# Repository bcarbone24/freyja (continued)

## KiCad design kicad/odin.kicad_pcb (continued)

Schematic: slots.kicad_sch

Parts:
C139, C140, C141, C142, C144, C146, C148, C150, C152, C154, C156, C158, C160, C162: 100nF; C_0402_1005Metric; LCSC C1525
C143, C145, C147, C149, C151, C153, C155, C157, C159, C161: 10uF; C_0805_2012Metric; LCSC C15850
C163, C164, C165, C166: 22uF; C_0805_2012Metric; LCSC C86816
F1, F2, F5, F6, F9, F10, F13, F14, F17, F18, F21, F22, F25, F26, F29, F30, F33, F34, F37, F38: 500mA; F1206; LCSC C269115
F3, F7, F11, F15, F19, F23, F27, F31, F35, F39: 300mA; F1206; LCSC C22378340
F4, F8, F12, F16, F20, F24, F28, F32, F36, F40: 1.1A 33V; Fuse_TECHFUSE_SMD2018; LCSC C70150
J3, J5: WingTAT 2044-2X32G00SA; HDR-TH_64P-P2.54-V-F-R2-C32-S2.54-1; LCSC C49569844
J7, J8: PM254-2-08-Z-8.5; HDR-TH_16P-P2.54-V-F-R2-C8-S2.54; LCSC C2897409
J19, J20: 2.54-2*3P; HDR-TH_6P-P2.54-V-M-R2-C3-S2.54-1; LCSC C65114
J53, J54, J55, J56, J57, J58, J62, J63, J64, J65: XFCN PM254V-11-07-H85; HDR-TH_7P-P2.54-V-F; LCSC C2832270
MK65, MK66, MK67, MK68, MK69, MK70, MK71, MK72, MK76, MK77: BOOMELE 2.54-1x40P-21mm; cut to 1P; hand/wave sol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; HDR-TH_1P-P2.54-V-M-21MM-C51353; LCSC C51353
R96, R97: 10k; R_0603_1608Metric
U9, U10: SN74LXC8T245PWR; TSSOP-24_L7.8-W4.4-P0.65-LS6.4-BL_1; LCSC C4363995

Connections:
+1V8_IO: C139.1, C141.1, J19.5, J20.5, R96.1, R97.1, U9.1 (VCCA), U10.1 (VCCA); also elsewhere on the board
+2V5: J19.3, J20.3; also elsewhere on the board
+3V3: J19.1, J20.1; also elsewhere on the board
+3V3_EXT: F1.1, F3.1, F5.1, F7.1, F11.1, F15.1, F19.1, F23.1, F27.1, F31.1, F35.1, F39.1; also elsewhere on the board
+5V: C140.1, C142.1, U9.23 (VCCB), U9.24 (VCCB), U10.23 (VCCB), U10.24 (VCCB); also elsewhere on the board
+5V_EXT: F2.1, F6.1, F10.1, F14.1, F18.1, F22.1, F26.1, F30.1, F34.1, F38.1; also elsewhere on the board
AUX_RAIL: F4.1, F8.1, F12.1, F16.1, F20.1, F24.1, F28.1, F32.1, F36.1, F40.1; also elsewhere on the board
BUS5V0_DIR: U9.2 (DIR); also elsewhere on the board
BUS5V0_IO0: U9.3 (A1); also elsewhere on the board
BUS5V0_IO1: U9.4 (A2); also elsewhere on the board
BUS5V0_IO2: U9.5 (A3); also elsewhere on the board
BUS5V0_IO3: U9.6 (A4); also elsewhere on the board
BUS5V0_IO4: U9.7 (A5); also elsewhere on the board
BUS5V0_IO5: U9.8 (A6); also elsewhere on the board
BUS5V0_IO6: U9.9 (A7); also elsewhere on the board
BUS5V0_IO7: U9.10 (A8); also elsewhere on the board
BUS5V0_OE_N: R96.2, U9.22 (~OE); also elsewhere on the board
BUS5V0_PIN0: J7.1, U9.21 (B1)
BUS5V0_PIN1: J7.2, U9.20 (B2)
BUS5V0_PIN2: J7.3, U9.19 (B3)
BUS5V0_PIN3: J7.4, U9.18 (B4)
BUS5V0_PIN4: J7.7, U9.17 (B5)
BUS5V0_PIN5: J7.8, U9.16 (B6)
BUS5V0_PIN6: J7.9, U9.15 (B7)
BUS5V0_PIN7: J7.10, U9.14 (B8)
BUS5V1_DIR: U10.2 (DIR); also elsewhere on the board
BUS5V1_IO0: U10.3 (A1); also elsewhere on the board
BUS5V1_IO1: U10.4 (A2); also elsewhere on the board
BUS5V1_IO2: U10.5 (A3); also elsewhere on the board
BUS5V1_IO3: U10.6 (A4); also elsewhere on the board
BUS5V1_IO4: U10.7 (A5); also elsewhere on the board
BUS5V1_IO5: U10.8 (A6); also elsewhere on the board
BUS5V1_IO6: U10.9 (A7); also elsewhere on the board
BUS5V1_IO7: U10.10 (A8); also elsewhere on the board
BUS5V1_OE_N: R97.2, U10.22 (~OE); also elsewhere on the board
BUS5V1_PIN0: J8.1, U10.21 (B1)
BUS5V1_PIN1: J8.2, U10.20 (B2)
BUS5V1_PIN2: J8.3, U10.19 (B3)
BUS5V1_PIN3: J8.4, U10.18 (B4)
BUS5V1_PIN4: J8.7, U10.17 (B5)
BUS5V1_PIN5: J8.8, U10.16 (B6)
BUS5V1_PIN6: J8.9, U10.15 (B7)
BUS5V1_PIN7: J8.10, U10.14 (B8)
GND: C139.2, C140.2, C141.2, C142.2, C143.2, C144.2, C145.2, C146.2, C147.2, C148.2, C149.2, C150.2, C151.2, C152.2, C153.2, C154.2, C155.2, C156.2, C157.2, C158.2, C159.2, C160.2, C161.2, C162.2, C163.2, C164.2, C165.2, C166.2, J3.5, J3.6, J3.11, J3.12, J3.21, J3.22, J3.27, J3.28, J3.37, J3.38, J3.43, J3.44, J3.53, J3.54, J3.59, J3.60, J5.5, J5.6, J5.11, J5.12, J5.21, J5.22, J5.27, J5.28, J5.37, J5.38, J5.43, J5.44, J5.53, J5.54, J5.59, J5.60, J7.5, J7.6, J7.11, J7.12, J8.5, J8.6, J8.11, J8.12, J53.2, J53.4, J53.6, J54.2, J54.4, J54.6, J55.2, J55.4, J55.6, J56.2, J56.4, J56.6, J57.2, J57.4, J57.6, J58.2, J58.4, J58.6, J62.2, J62.4, J62.6, J63.2, J63.4, J63.6, J64.2, J64.4, J64.6, J65.2, J65.4, J65.6, MK65.1, MK66.1, MK67.1, MK68.1, MK69.1, MK70.1, MK71.1, MK72.1, MK76.1, MK77.1, U9.11 (GND), U9.12 (GND), U9.13 (GND), U10.11 (GND), U10.12 (GND), U10.13 (GND); also elsewhere on the board
SLOTA_IO0: J3.1; also elsewhere on the board
SLOTA_IO1: J3.2; also elsewhere on the board
SLOTA_IO2: J3.3; also elsewhere on the board
SLOTA_IO3: J3.4; also elsewhere on the board
SLOTA_IO4: J3.7; also elsewhere on the board
SLOTA_IO5: J3.8; also elsewhere on the board
SLOTA_IO6: J3.9; also elsewhere on the board
SLOTA_IO7: J3.10; also elsewhere on the board
SLOTA_IO8: J3.13; also elsewhere on the board
SLOTA_IO9: J3.14; also elsewhere on the board
SLOTA_IO10: J3.15; also elsewhere on the board
SLOTA_IO11: J3.16; also elsewhere on the board
SLOTB_IO0: J3.17; also elsewhere on the board
SLOTB_IO1: J3.18; also elsewhere on the board
SLOTB_IO2: J3.19; also elsewhere on the board
SLOTB_IO3: J3.20; also elsewhere on the board
SLOTB_IO4: J3.23; also elsewhere on the board
SLOTB_IO5: J3.24; also elsewhere on the board
SLOTB_IO6: J3.25; also elsewhere on the board
SLOTB_IO7: J3.26; also elsewhere on the board
SLOTB_IO8: J3.29; also elsewhere on the board
SLOTB_IO9: J3.30; also elsewhere on the board
SLOTB_IO10: J3.31; also elsewhere on the board
SLOTB_IO11: J3.32; also elsewhere on the board
SLOTC_IO0: J3.33; also elsewhere on the board
SLOTC_IO1: J3.34; also elsewhere on the board
SLOTC_IO2: J3.35; also elsewhere on the board
SLOTC_IO3: J3.36; also elsewhere on the board
SLOTC_IO4: J3.39; also elsewhere on the board
SLOTC_IO5: J3.40; also elsewhere on the board
SLOTC_IO6: J3.41; also elsewhere on the board
SLOTC_IO7: J3.42; also elsewhere on the board
SLOTC_IO8: J3.45; also elsewhere on the board
SLOTC_IO9: J3.46; also elsewhere on the board
SLOTC_IO10: J3.47; also elsewhere on the board
SLOTC_IO11: J3.48; also elsewhere on the board
SLOTD_IO0: J3.49; also elsewhere on the board
SLOTD_IO1: J3.50; also elsewhere on the board
SLOTD_IO2: J3.51; also elsewhere on the board
SLOTD_IO3: J3.52; also elsewhere on the board
SLOTD_IO4: J3.55; also elsewhere on the board
SLOTD_IO5: J3.56; also elsewhere on the board
SLOTD_IO6: J3.57; also elsewhere on the board
SLOTD_IO7: J3.58; also elsewhere on the board
SLOTD_IO8: J3.61; also elsewhere on the board
SLOTD_IO9: J3.62; also elsewhere on the board
SLOTD_IO10: J3.63; also elsewhere on the board
SLOTD_IO11: J3.64; also elsewhere on the board
SLOTE_IO0: J5.64; also elsewhere on the board
SLOTE_IO1: J5.63; also elsewhere on the board
SLOTE_IO2: J5.62; also elsewhere on the board
SLOTE_IO3: J5.61; also elsewhere on the board
SLOTE_IO4: J5.58; also elsewhere on the board
SLOTE_IO5: J5.57; also elsewhere on the board
SLOTE_IO6: J5.56; also elsewhere on the board
SLOTE_IO7: J5.55; also elsewhere on the board
SLOTE_IO8: J5.52; also elsewhere on the board
SLOTE_IO9: J5.51; also elsewhere on the board
SLOTE_IO10: J5.50; also elsewhere on the board
SLOTE_IO11: J5.49; also elsewhere on the board
SLOTF_IO0: J5.48; also elsewhere on the board
SLOTF_IO1: J5.47; also elsewhere on the board
SLOTF_IO2: J5.46; also elsewhere on the board
SLOTF_IO3: J5.45; also elsewhere on the board
SLOTF_IO4: J5.42; also elsewhere on the board
SLOTF_IO5: J5.41; also elsewhere on the board
SLOTF_IO6: J5.40; also elsewhere on the board
SLOTF_IO7: J5.39; also elsewhere on the board
SLOTF_IO8: J5.36; also elsewhere on the board
SLOTF_IO9: J5.35; also elsewhere on the board
SLOTF_IO10: J5.34; also elsewhere on the board
SLOTF_IO11: J5.33; also elsewhere on the board
SLOTG_IO0: J5.32; also elsewhere on the board
SLOTG_IO1: J5.31; also elsewhere on the board
SLOTG_IO2: J5.30; also elsewhere on the board
SLOTG_IO3: J5.29; also elsewhere on the board
SLOTG_IO4: J5.26; also elsewhere on the board
SLOTG_IO5: J5.25; also elsewhere on the board
SLOTG_IO6: J5.24; also elsewhere on the board
SLOTG_IO7: J5.23; also elsewhere on the board
SLOTG_IO8: J5.20; also elsewhere on the board
SLOTG_IO9: J5.19; also elsewhere on the board
SLOTG_IO10: J5.18; also elsewhere on the board
SLOTG_IO11: J5.17; also elsewhere on the board
SLOTH_IO0: J5.16; also elsewhere on the board
SLOTH_IO1: J5.15; also elsewhere on the board
SLOTH_IO2: J5.14; also elsewhere on the board
SLOTH_IO3: J5.13; also elsewhere on the board
SLOTH_IO4: J5.10; also elsewhere on the board
SLOTH_IO5: J5.9; also elsewhere on the board
SLOTH_IO6: J5.8; also elsewhere on the board
SLOTH_IO7: J5.7; also elsewhere on the board
SLOTH_IO8: J5.4; also elsewhere on the board
SLOTH_IO9: J5.3; also elsewhere on the board
SLOTH_IO10: J5.2; also elsewhere on the board
SLOTH_IO11: J5.1; also elsewhere on the board
SLOT_A_3V3: C148.1, F11.2, J53.3
SLOT_A_5V: F10.2, J53.5
SLOT_A_AUX: F12.2, J53.7
SLOT_A_PIN_VOLTAGE: C147.1, F9.2, J53.1
SLOT_B_3V3: C150.1, F15.2, J62.3
SLOT_B_5V: F14.2, J62.5
SLOT_B_AUX: F16.2, J62.7
SLOT_B_PIN_VOLTAGE: C149.1, F13.2, J62.1
SLOT_C_3V3: C152.1, F19.2, J54.3
SLOT_C_5V: F18.2, J54.5
SLOT_C_AUX: F20.2, J54.7
SLOT_C_PIN_VOLTAGE: C151.1, F17.2, J54.1
SLOT_D_3V3: C154.1, F23.2, J63.3
SLOT_D_5V: F22.2, J63.5
SLOT_D_AUX: F24.2, J63.7
SLOT_D_PIN_VOLTAGE: C153.1, F21.2, J63.1
SLOT_E_3V3: C156.1, F27.2, J55.3
SLOT_E_5V: F26.2, J55.5
SLOT_E_AUX: F28.2, J55.7
SLOT_E_PIN_VOLTAGE: C155.1, F25.2, J55.1
SLOT_F_3V3: C158.1, F31.2, J64.3
SLOT_F_5V: F30.2, J64.5
SLOT_F_AUX: F32.2, J64.7
SLOT_F_PIN_VOLTAGE: C157.1, F29.2, J64.1
SLOT_G_3V3: C160.1, F35.2, J56.3
SLOT_G_5V: F34.2, J56.5
SLOT_G_AUX: F36.2, J56.7
SLOT_G_PIN_VOLTAGE: C159.1, F33.2, J56.1
SLOT_H_3V3: C162.1, F39.2, J65.3
SLOT_H_5V: F38.2, J65.5
SLOT_H_AUX: F40.2, J65.7
SLOT_H_PIN_VOLTAGE: C161.1, F37.2, J65.1
SLOT_L_3V3: C144.1, F3.2, J57.3
SLOT_L_5V: F2.2, J57.5
SLOT_L_AUX: F4.2, J57.7
SLOT_L_PIN_VOLTAGE: C143.1, F1.2, J57.1
SLOT_M_3V3: C146.1, F7.2, J58.3
SLOT_M_5V: F6.2, J58.5
SLOT_M_AUX: F8.2, J58.7
SLOT_M_PIN_VOLTAGE: C145.1, F5.2, J58.1
VCCIO_1: C163.1, C164.1, J19.2, J19.4, J19.6; also elsewhere on the board
VCCIO_1_EXT: F9.1, F13.1, F17.1, F21.1; also elsewhere on the board
VCCIO_2: C165.1, C166.1, J20.2, J20.4, J20.6; also elsewhere on the board
VCCIO_2_EXT: F25.1, F29.1, F33.1, F37.1; also elsewhere on the board

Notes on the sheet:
SLOTS — Ten keyed extension ports, branch fusing and level shifting — HW 0.1.0-proto.1
5V BUS 0 converter
Lets the FPGA (3.3 V) talk to 5 V extensions on slot L. U9 shifts eight lines between 3.3 V and 5 V, all in one direction at a time (BUS5V0_DIR). It stays off until the FPGA pulls BUS5V0_OE_N low; the pull-up keeps the bus off while the FPGA is still loading.
5V BUS 1 converter
Same as 5V BUS 0, for slot M: U10 shifts eight lines between the FPGA's 3.3 V and 5 V, direction BUS5V1_DIR, off until BUS5V1_OE_N goes low.
SHIELD HEADER ABCD
One long 2x32 socket on the right edge carrying the signals of slots A, B, C and D: twelve FPGA pins each (bank 15), with grounds between groups. Their voltage is whatever J19 selects.
SHIELD HEADER EFGH
One long 2x32 socket on the left edge carrying the signals of slots E, F, G and H: twelve FPGA pins each (bank 34), voltage set by J20.
SHIELD HEADER L
The signal socket of slot L (5V BUS 0): eight 5 V data lines from U9, with four grounds between them.
SHIELD HEADER M
The signal socket of slot M (5V BUS 1): eight 5 V data lines from U10, with four grounds between them.
SLOT L branches
Power for whatever is plugged into slot L. The 1x7 power socket carries PIN V (3.3 V), 3.3 V, 5 V and AUX, each beside a ground, and each through its own resettable fuse, so a short on one extension trips only that slot's fuse and the rest of the board keeps running. The long grounded pin in front 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
SLOT M branches
Power for whatever is plugged into slot M. The 1x7 power socket carries PIN V (3.3 V), 3.3 V, 5 V and AUX, each beside a ground, and each through its own resettable fuse, so a short on one extension trips only that slot's fuse and the rest of the board keeps running. The long grounded pin in front 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
SLOT A branches
Power for whatever is plugged into slot A. The 1x7 power socket carries PIN V (the J19 voltage), 3.3 V, 5 V and AUX, each beside a ground, and each through its own resettable fuse, so a short on one extension trips only that slot's fuse and the rest of the board keeps running. The long grounded pin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
SLOT B branches
Power for whatever is plugged into slot B. The 1x7 power socket carries PIN V (the J19 voltage), 3.3 V, 5 V and AUX, each beside a ground, and each through its own resettable fuse, so a short on one extension trips only that slot's fuse and the rest of the board keeps running. The long grounded pin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
SLOT C branches
Power for whatever is plugged into slot C. The 1x7 power socket carries PIN V (the J19 voltage), 3.3 V, 5 V and AUX, each beside a ground, and each through its own resettable fuse, so a short on one extension trips only that slot's fuse and the rest of the board keeps running. The long grounded pin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
SLOT D branches
Power for whatever is plugged into slot D. The 1x7 power socket carries PIN V (the J19 voltage), 3.3 V, 5 V and AUX, each beside a ground, and each through its own resettable fuse, so a short on one extension trips only that slot's fuse and the rest of the board keeps running. The long grounded pin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
SLOT E branches
Power for whatever is plugged into slot E. The 1x7 power socket carries PIN V (the J20 voltage), 3.3 V, 5 V and AUX, each beside a ground, and each through its own resettable fuse, so a short on one extension trips only that slot's fuse and the rest of the board keeps running. The long grounded pin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
SLOT F branches
Power for whatever is plugged into slot F. The 1x7 power socket carries PIN V (the J20 voltage), 3.3 V, 5 V and AUX, each beside a ground, and each through its own resettable fuse, so a short on one extension trips only that slot's fuse and the rest of the board keeps running. The long grounded pin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
SLOT G branches
Power for whatever is plugged into slot G. The 1x7 power socket carries PIN V (the J20 voltage), 3.3 V, 5 V and AUX, each beside a ground, and each through its own resettable fuse, so a short on one extension trips only that slot's fuse and the rest of the board keeps running. The long grounded pin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
SLOT H branches
Power for whatever is plugged into slot H. The 1x7 power socket carries PIN V (the J20 voltage), 3.3 V, 5 V and AUX, each beside a ground, and each through its own resettable fuse, so a short on one extension trips only that slot's fuse and the rest of the board keeps running. The long grounded pin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
VCCIO_1 selector
Jumper that picks the signal voltage of slots A-D: one shunt on J19 selects 3.3, 2.5 or 1.8 V. It powers FPGA bank 15 and the PIN V pin of those four slots. One position only; change it with the board unpowered.
VCCIO_2 selector
Jumper that picks the signal voltage of slots E-H (J20): 3.3, 2.5 or 1.8 V for FPGA bank 34 and those slots' PIN V pin.
Power flags for the rails made on this page

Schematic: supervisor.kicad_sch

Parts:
C116, C117, C118, C119, C120, C121, C122, C123, C124, C125, C126, C127, C128, C129, C135, C136, C138: 100nF; C_0402_1005Metric; LCSC C1525
C130, C131, C132: 4.7uF; C_0603_1608Metric; LCSC C277476
C133, C134: 15pF; C_0402_1005Metric
C137: 1uF; C_0402_1005Metric
D6: ESDA6V1BC6; SOT-23-6_L2.9-W1.6-P0.95-LS2.8-BR; LCSC C495220
D7: SMBJ13A-TR; SMB_L4.6-W3.6-LS5.3-RD; LCSC C133675
D9, D10, D11: F.0603.00025/P2-0603G1TS2-06T-002; LED0603-RD_GREEN; LCSC C7496818
J1: USB-C; USB_C_Receptacle_HCTL_HC-TYPE-C-16P-01A_Odin; LCSC C2894897
J2: FPGA JTAG; IDC-TH_10P-P2.54_C5665; LCSC C5665
J51: CTRL SWD; CONN-SMD-3P-P1.00_BM03B-SRSS-TB-LF-SN; LCSC C160389
J52: PZ254V-11-02P; HDR-TH_2P-P2.54-V-M; LCSC C492401
L1: 3.3uH AOTA-B201610S3R3-101-T; IND-SMD_L2.0-W1.6_AOTA-B201610S3R3-101-T; LCSC C42411119
Q3: BSS138LT1G; SOT-23-3_L2.9-W1.6-P1.90-LS2.8-BR; LCSC C82045
R8, R14, R15, R16, R17, R18, R19, R20, R21, R22, R23, R24, R25, R26, R27, R28, R29, R30, R31, R32: 33; R_0402_1005Metric; LCSC C25105
R9, R10, R12, R128, R129, R130: 1k; R_0402_1005Metric; LCSC C11702
R11, R172: 10k; R_0402_1005Metric
R13: 10k; R_0402_1005Metric; not fitted
R33: 0; R_0402_1005Metric
R34: 10k; R_0603_1608Metric
R170, R171: 27; R_0402_1005Metric
R173: 100k; R_0402_1005Metric; LCSC C25741
SW1: CTRL BOOT; KEY-SMD_B3U-1000PM; LCSC C231329
U7: RP2350B; QFN-80_L10.0-W10.0-P0.40-TL-EP3.4; LCSC C42415655
U8: W25Q32JVZP; WSON-8_L6.0-W5.0-P1.27-BL-EP; LCSC C571260
U18: CH224K; ESSOP-10_L4.9-W3.9-P1.0-LS6.0-TL-EP; LCSC C970725
U20: SN74CB3Q3384APWR; TSSOP-24_L7.8-W4.4-P0.65-LS6.4-BL; LCSC C469874
Y1: 12MHz ABM8-272-T3; CRYSTAL-SMD_4P-L3.2-W2.5-BL; LCSC C20625731

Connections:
+1V1: C127.1, C128.1, C129.1, C131.1, L1.1, U7.10 (DVDD), U7.32 (DVDD), U7.51 (DVDD), U7.65 (VREG_FB)
+3V3: C116.1, C117.1, C118.1, C119.1, C120.1, C121.1, C122.1, C123.1, C124.1, C125.1, C126.1, C130.1, C136.1, C138.1, J2.1, J52.1, R8.1, R10.1, R11.1, R13.1, R128.1, R129.1, R130.1, U7.5 (IOVDD), U7.15 (IOVDD), U7.24 (IOVDD), U7.29 (IOVDD), U7.41 (IOVDD), U7.50 (IOVDD), U7.59 (ADC_AVDD), U7.60 (IOVDD), U7.64 (VREG_VIN), U7.68 (USB_OTP_VDD), U7.69 (QSPI_IOVDD), U7.76 (IOVDD), U8.8 (VCC), U20.13 (~2OE), U20.24 (VCC); also elsewhere on the board
BOOTSEL_SW: R12.2, SW1.1
CFG_CCLK: R21.2; also elsewhere on the board
CFG_DONE: R20.2; also elsewhere on the board
CFG_INIT_B: R19.2; also elsewhere on the board
CFG_PROG_B: R18.2; also elsewhere on the board
CORE_1V0_GOOD: U7.47 (GPIO38); also elsewhere on the board
DBG_TCK: R27.2; also elsewhere on the board
DBG_TDI: R29.2; also elsewhere on the board
DBG_TDO: R30.2; also elsewhere on the board
DBG_TMS: R28.2; also elsewhere on the board
EN_1V0: U7.25 (GPIO24); also elsewhere on the board
EN_1V2: U7.26 (GPIO25); also elsewhere on the board
EN_2V5: U7.22 (GPIO22); also elsewhere on the board
EXTERNAL_JTAG_SELECTED: J52.2, R34.1, U20.1 (~1OE)
EXT_EN: U7.6 (GPIO8); also elsewhere on the board
EXT_FAULT: U7.43 (GPIO34); also elsewhere on the board
FLASH_CS_B: R22.2; also elsewhere on the board
FLASH_D0_MOSI: R23.2; also elsewhere on the board
FLASH_D1_MISO: R24.2; also elsewhere on the board
FLASH_D2_WP: R25.2; also elsewhere on the board
FLASH_D3_HOLD: R26.2; also elsewhere on the board
GND: C116.2, C117.2, C118.2, C119.2, C120.2, C121.2, C122.2, C123.2, C124.2, C125.2, C126.2, C127.2, C128.2, C129.2, C130.2, C131.2, C132.2, C133.2, C134.2, C135.2, C136.2, C137.2, C138.2, D6.2 (COM), D6.5 (COM), D7.2 (A), J1.A1 (GND), J1.A12 (GND), J1.B1 (GND), J1.B12 (GND), J1.SH (SHIELD), J2.2, J2.4, J2.6, J2.8, J2.10, J51.2, Q3.2 (S), R34.2, R173.2, SW1.2, U7.62 (VREG_PGND), U7.81 (GND), U8.4 (GND), U8.9 (EP), U18.2 (CFG2), U18.3 (CFG3), U18.11 (GND), U20.12 (GND), Y1.2 (G), Y1.4 (G); also elsewhere on the board
JTAG_TCK: J2.5, U20.2 (1B1); also elsewhere on the board
JTAG_TDI: J2.9, U20.6 (1B3); also elsewhere on the board
JTAG_TDO: J2.7, R33.2; also elsewhere on the board
JTAG_TDO_SW: R33.1, U20.9 (1B4)
JTAG_TMS: J2.3, U20.5 (1B2); also elsewhere on the board
LED_HEARTBEAT_A: D9.2 (A), R128.2
LED_HEARTBEAT_N: D9.1 (C), U7.44 (GPIO35)
LED_USER1_A: D10.2 (A), R129.2
LED_USER1_N: D10.1 (C), U7.45 (GPIO36)
LED_USER2_A: D11.2 (A), R130.2
LED_USER2_N: D11.1 (C), U7.46 (GPIO37)
MON_1V0: U7.56 (GPIO45/ADC5); also elsewhere on the board
MON_1V8: U7.55 (GPIO44/ADC4); also elsewhere on the board
MON_2V5: U7.54 (GPIO43/ADC3); also elsewhere on the board
MON_3V3: U7.53 (GPIO42/ADC2); also elsewhere on the board
MON_5V: U7.52 (GPIO41/ADC1); also elsewhere on the board
MON_VCCIO_1: U7.57 (GPIO46/ADC6); also elsewhere on the board
MON_VCCIO_2: U7.58 (GPIO47/ADC7); also elsewhere on the board
MON_VSYS: U7.49 (GPIO40/ADC0); also elsewhere on the board
PD_CFG1: Q3.3 (D), R172.2, U18.9 (CFG1)
PD_PG: R11.2, U7.38 (GPIO30), U18.10 (PG)
PD_REQ_9V: Q3.1 (G), R173.1, U7.28 (GPIO27); also elsewhere on the board
PD_VDD: C137.1, R172.1, U18.1 (VDD)
SB_UART_RX: R31.2; also elsewhere on the board
SB_UART_TX: R32.2; also elsewhere on the board
SUPF_CLK: U7.71 (QSPI_SCLK), U8.6 (CLK)
SUPF_CS: R12.1, R13.2, U7.75 (~QSPI_SS), U8.1 (~CS)
SUPF_D0: U7.72 (QSPI_SD0), U8.5 (DI/IO_{0})
SUPF_D1: U7.74 (QSPI_SD1), U8.2 (DO/IO_{1})
SUPF_D2: U7.73 (QSPI_SD2), U8.3 (~WP/IO_{2})
SUPF_D3: U7.70 (QSPI_SD3), U8.7 (~HOLD/~RESET/IO_{3})
SUP_CCLK: R21.1, U7.8 (GPIO10)
SUP_DBG_TCK: R27.1, U7.14 (GPIO15)
SUP_DBG_TDI: R29.1, U7.17 (GPIO17)
SUP_DBG_TDO: R30.1, U7.18 (GPIO18)
SUP_DBG_TMS: R28.1, U7.16 (GPIO16)
SUP_DONE: R20.1, U7.3 (GPIO6)
SUP_FCS_B: R22.1, U7.7 (GPIO9)
SUP_FD0: R23.1, U7.9 (GPIO11)
SUP_FD1: R24.1, U7.11 (GPIO12)
SUP_FD2: R25.1, U7.12 (GPIO13)
SUP_FD3: R26.1, U7.4 (GPIO7)
SUP_INIT_B: R19.1, U7.2 (GPIO5)
SUP_JTAG_TCK: R14.1, U7.77 (GPIO0)
SUP_JTAG_TDI: R16.1, U7.79 (GPIO2)
SUP_JTAG_TDO: R17.1, U7.80 (GPIO3)
SUP_JTAG_TMS: R15.1, U7.78 (GPIO1)
SUP_LX: L1.2, U7.63 (VREG_LX)
SUP_PROG_B: R18.1, U7.1 (GPIO4)
SUP_RUN: C135.1, R10.2, U7.35 (RUN)
SUP_SWCLK: J51.1, U7.33 (SWCLK)
SUP_SWDIO: J51.3, U7.34 (SWDIO)
SUP_UART_RX: R32.1, U7.42 (GPIO33)
SUP_UART_TX: R31.1, U7.40 (GPIO32)
SUP_VREG_AVDD: C132.1, R8.2, U7.61 (VREG_AVDD)
SUP_XIN: C133.1, U7.30 (XIN), Y1.1
SUP_XOUT: R9.1, U7.31 (XOUT)
SUP_XTAL_OUT: C134.1, R9.2, Y1.3
SWJ_TCK: R14.2, U20.3 (1A1)
SWJ_TDI: R16.2, U20.7 (1A3)
SWJ_TDO: R17.2, U20.8 (1A4)
SWJ_TMS: R15.2, U20.4 (1A2)
USB_CC1: D6.4 (TVS3), J1.A5 (CC1), U18.7 (CC1)
USB_CC2: D6.6 (TVS4), J1.B5 (CC2), U18.6 (CC2)
USB_DM: D6.3 (TVS2), J1.A7 (D-), J1.B7 (D-), R171.1
USB_DM_MCU: R171.2, U7.66 (USB_DM)
USB_DP: D6.1 (TVS1), J1.A6 (D+), J1.B6 (D+), R170.1
USB_DP_MCU: R170.2, U7.67 (USB_DP)
VBUS: D7.1 (K), J1.A4 (VBUS), J1.A9 (VBUS), J1.B4 (VBUS), J1.B9 (VBUS), U18.8 (VBUS); also elsewhere on the board
VBUS5_ST: U7.21 (GPIO21); also elsewhere on the board

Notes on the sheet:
SUPERVISOR — Board controller: RP2350B, USB-C, startup memory and FPGA control — HW 0.1.0-proto.1
U7 board controller
The board controller, a Raspberry Pi RP2350B microcontroller that is always on. It is what the USB cable talks to: it loads designs into the FPGA over JTAG or writes them to the FPGA's flash, turns the supplies on in order and watches them, asks a USB-PD charger for 9 V, enables extension power, an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
U7 core regulator (RP-008280 s2.1)
Parts for the RP2350's built-in switching regulator, which makes its 1.1 V core supply (+1V1) from +3V3. Values and the inductor are the ones Raspberry Pi specifies in their hardware design guide (RP-008280 section 2.1).
crystal (RP-008280 s4)
The board controller's 12 MHz clock: the exact crystal, load capacitors and 1 k drive-limiting resistor Raspberry Pi specifies (RP-008280 section 4).
RUN
The board controller's reset input. The pull-up keeps it running; the capacitor holds it in reset briefly at power-on until +3V3 is stable.
board controller startup memory
The board controller's own 4 MB flash, holding its firmware. Separate from the FPGA's flash.
USB-C
The main connector: power in, and the USB link to your computer for programming and talking to the board.
USB protection
Clamps for static discharge and voltage spikes on the USB connector: D6 on the data and CC lines, D7 on the power line (VBUS).
USB-PD sink
Negotiates the supply voltage with a USB-PD charger. Out of the box it asks for 5 V: CFG1 is pulled up to the chip's own 3.3 V and CFG2/CFG3 are grounded, so the only other request the pins can form is 9 V, which the board controller selects by turning Q3 on (PD_REQ_9V). A dead or resetting control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
BOOTSEL
Hold CTRL BOOT while plugging in USB to put the board controller in its built-in USB bootloader, for installing or recovering its firmware. The 1 k resistor lets the button win without fighting the chip. The 10 k pull-up is not fitted, as in Raspberry Pi's design.
board controller SWD
Debug connector for the board controller's own processor (SWD): for developing its firmware with a debug probe. Not for the FPGA.
series resistors to FPGA
One 33 ohm resistor on every wire between the board controller and the FPGA: JTAG, the configuration pins, the FPGA flash bus, the debug sideband and the UART. They limit current if both sides ever drive the same wire at once, and damp ringing.
JTAG owner selection
Decides who programs the FPGA over JTAG. Normally (J52 open) the board controller does, through the U20 switch. Fit a jumper on J52 and U20 disconnects the board controller completely, so an external programmer plugged into J2 has the FPGA to itself. A jumper, not software, so it works even when th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
manual JTAG header
Standard 2x5 JTAG header for an external FPGA programmer (Xilinx/AMD cable or similar). Fit J52 first.
board status LEDs
Three green LEDs on board controller GPIO35-37, lit by driving the pin low: CTRL HB blinks while the board controller firmware is alive; USER 1 and USER 2 are for software. Each has a 1 k current-limiting resistor from +3V3. Rules: ref/status-leds.md.
U7 USB series resistors
Two 27 ohm resistors in the USB data lines, right at the board controller, as Raspberry Pi's hardware design guide (section 5.1) asks. The ESD clamp D6 stays at the connector.
Power flags for the rails made on this page

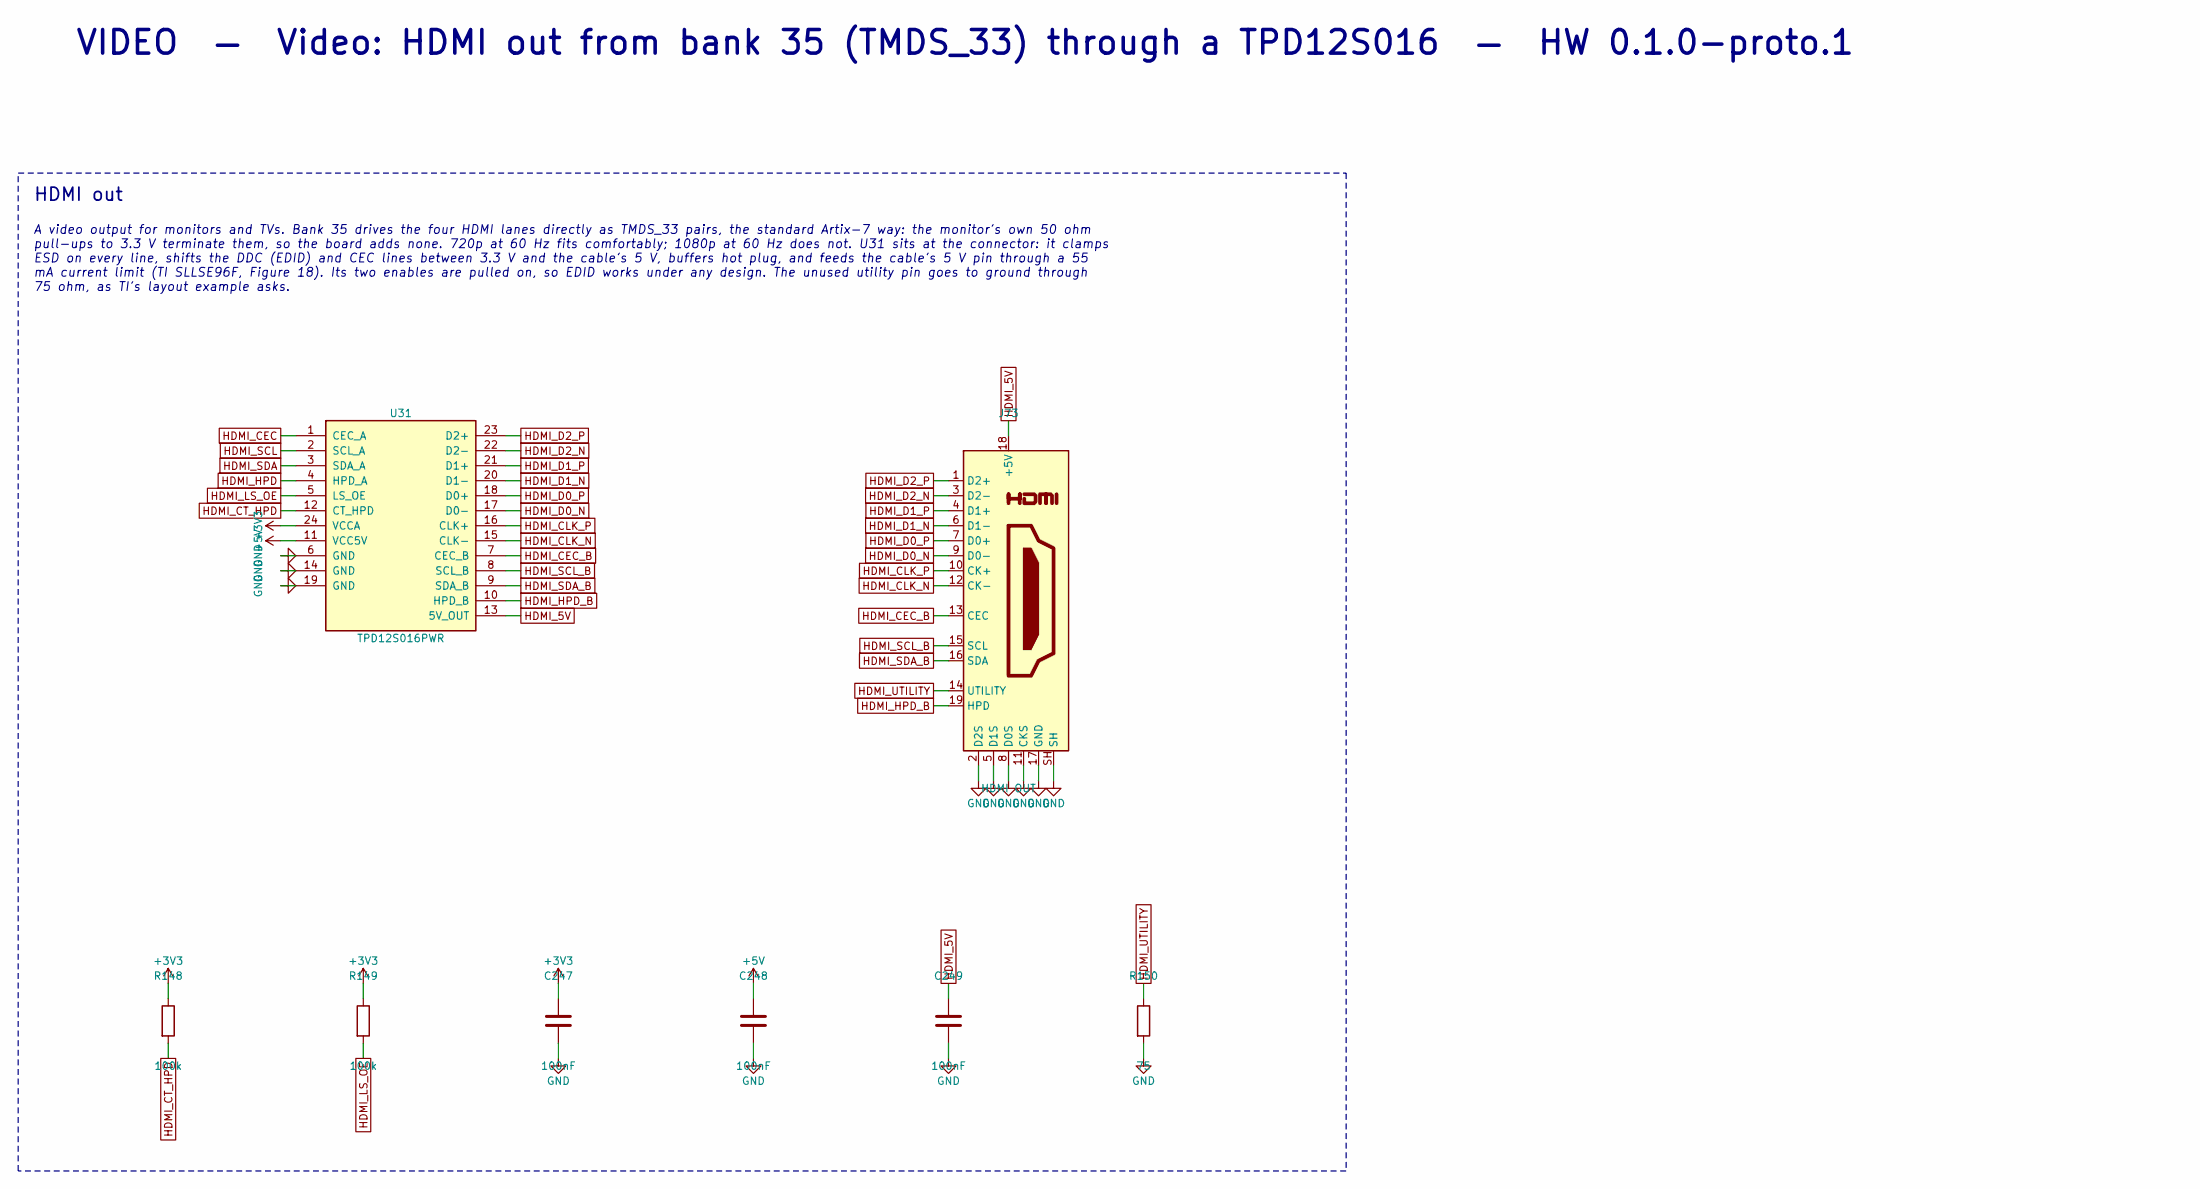
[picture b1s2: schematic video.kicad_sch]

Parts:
C247, C248, C249: 100nF; C_0402_1005Metric; LCSC C1525
J73: HDMI OUT; HDMI_A_Amphenol_10029449-x01xLF_Horizontal; LCSC C428493
R148, R149: 100k; R_0402_1005Metric; LCSC C25741
R150: 75; R_0402_1005Metric
U31: TPD12S016PWR; TSSOP-24_4.4x7.8mm_P0.65mm; LCSC C201665

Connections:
+3V3: C247.1, R148.1, R149.1, U31.24 (VCCA); also elsewhere on the board
+5V: C248.1, U31.11 (VCC5V); also elsewhere on the board
GND: C247.2, C248.2, C249.2, J73.2 (D2S), J73.5 (D1S), J73.8 (D0S), J73.11 (CKS), J73.17 (GND), J73.SH, R150.2, U31.6 (GND), U31.14 (GND), U31.19 (GND); also elsewhere on the board
HDMI_5V: C249.1, J73.18 (+5V), U31.13 (5V_OUT)
HDMI_CEC: U31.1 (CEC_A); also elsewhere on the board
HDMI_CEC_B: J73.13 (CEC), U31.7 (CEC_B)
HDMI_CLK_N: J73.12 (CK-), U31.15 (CLK-); also elsewhere on the board
HDMI_CLK_P: J73.10 (CK+), U31.16 (CLK+); also elsewhere on the board
HDMI_CT_HPD: R148.2, U31.12 (CT_HPD); also elsewhere on the board
HDMI_D0_N: J73.9 (D0-), U31.17 (D0-); also elsewhere on the board
HDMI_D0_P: J73.7 (D0+), U31.18 (D0+); also elsewhere on the board
HDMI_D1_N: J73.6 (D1-), U31.20 (D1-); also elsewhere on the board
HDMI_D1_P: J73.4 (D1+), U31.21 (D1+); also elsewhere on the board
HDMI_D2_N: J73.3 (D2-), U31.22 (D2-); also elsewhere on the board
HDMI_D2_P: J73.1 (D2+), U31.23 (D2+); also elsewhere on the board
HDMI_HPD: U31.4 (HPD_A); also elsewhere on the board
HDMI_HPD_B: J73.19 (HPD), U31.10 (HPD_B)
HDMI_LS_OE: R149.2, U31.5 (LS_OE); also elsewhere on the board
HDMI_SCL: U31.2 (SCL_A); also elsewhere on the board
HDMI_SCL_B: J73.15 (SCL), U31.8 (SCL_B)
HDMI_SDA: U31.3 (SDA_A); also elsewhere on the board
HDMI_SDA_B: J73.16 (SDA), U31.9 (SDA_B)
HDMI_UTILITY: J73.14 (UTILITY), R150.1

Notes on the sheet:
VIDEO — Video: HDMI out from bank 35 (TMDS_33) through a TPD12S016 — HW 0.1.0-proto.1
HDMI out
A video output for monitors and TVs. Bank 35 drives the four HDMI lanes directly as TMDS_33 pairs, the standard Artix-7 way: the monitor's own 50 ohm pull-ups to 3.3 V terminate them, so the board adds none. 720p at 60 Hz fits comfortably; 1080p at 60 Hz does not. U31 sits at the connector: it clam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

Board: 8 copper layers, 548 parts (0 on the bottom side), 497 nets, no tracks yet.
